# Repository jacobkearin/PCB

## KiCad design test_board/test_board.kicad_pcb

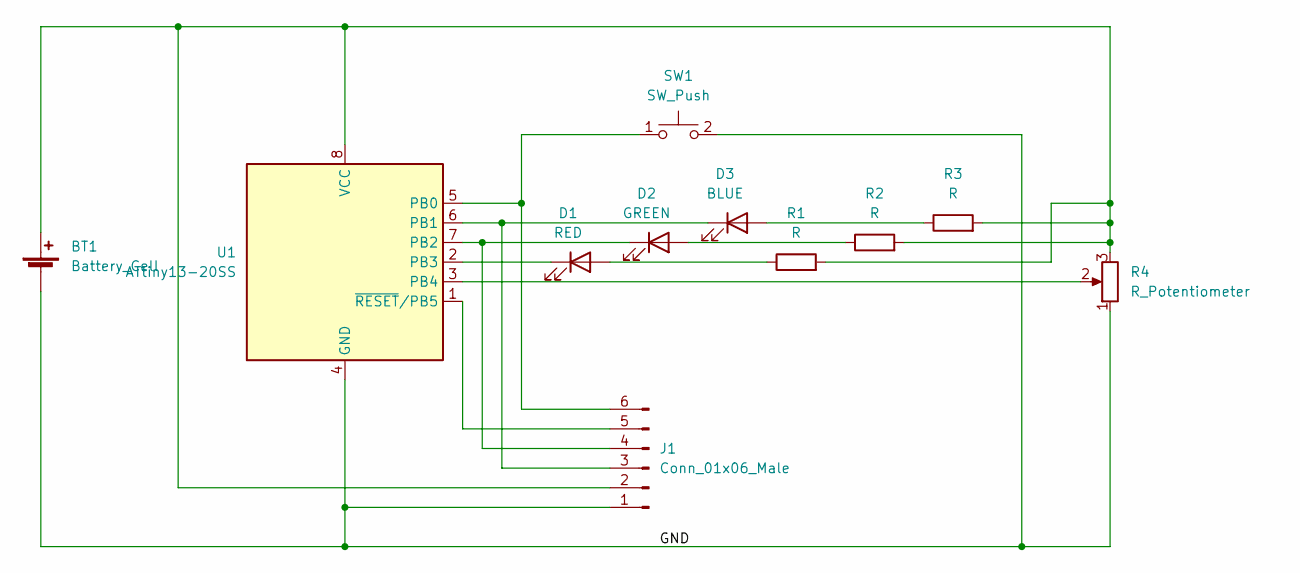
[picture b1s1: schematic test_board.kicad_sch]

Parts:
BT1: Battery_Cell; BatteryHolder_Keystone_103_1x20mm
D1: RED; LED_1206_3216Metric
D2: GREEN; LED_1206_3216Metric
D3: BLUE; LED_1206_3216Metric
J1: Conn_01x06_Male; PinHeader_2x03_P2.54mm_Vertical
R1, R2, R3: R; R_0805_2012Metric
R4: R_Potentiometer; Potentiometer_Bourns_3339P_Vertical
SW1: SW_Push; CK PTS635SL43 LFS
U1: ATtiny13-20SS; SOIC-8_3.9x4.9mm_P1.27mm

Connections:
/GND: BT1.2 (-), J1.1, R4.1, SW1.2, U1.4 (GND)
unnamed: BT1.1 (+), J1.2, R1.2, R2.2, R3.2, R4.3, U1.8 (VCC)
unnamed: D1.1 (K), U1.2 (PB3)
unnamed: D1.2 (A), R1.1
unnamed: D2.1 (K), J1.4, U1.7 (PB2)
unnamed: D2.2 (A), R2.1
unnamed: D3.1 (K), J1.3, U1.6 (PB1)
unnamed: D3.2 (A), R3.1
unnamed: J1.5, U1.1 (~RESET/PB5)
unnamed: J1.6, SW1.1, U1.5 (PB0)
unnamed: R4.2, U1.3 (PB4)

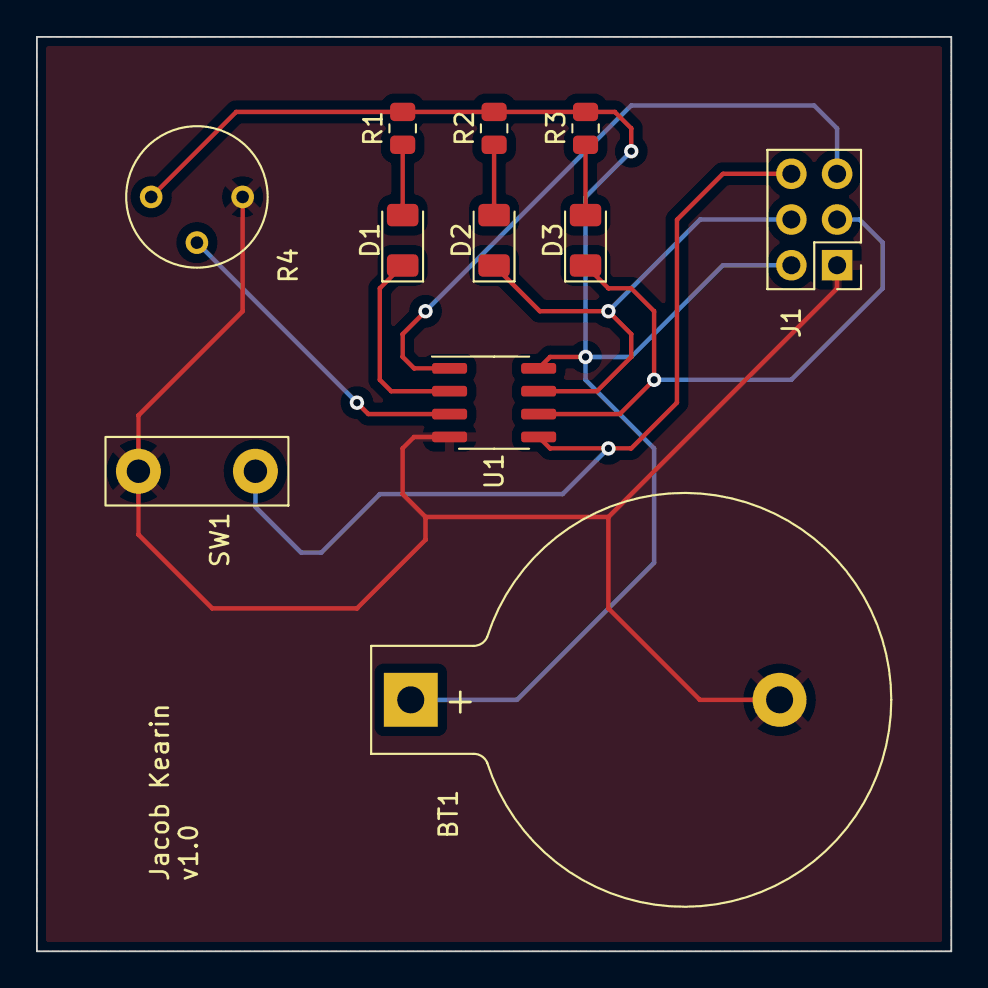
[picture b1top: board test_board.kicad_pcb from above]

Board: 2 copper layers, 50.8 x 50.8 mm, 11 parts (0 on the bottom side), 11 nets.

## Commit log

2022-11-01 test_project commit
